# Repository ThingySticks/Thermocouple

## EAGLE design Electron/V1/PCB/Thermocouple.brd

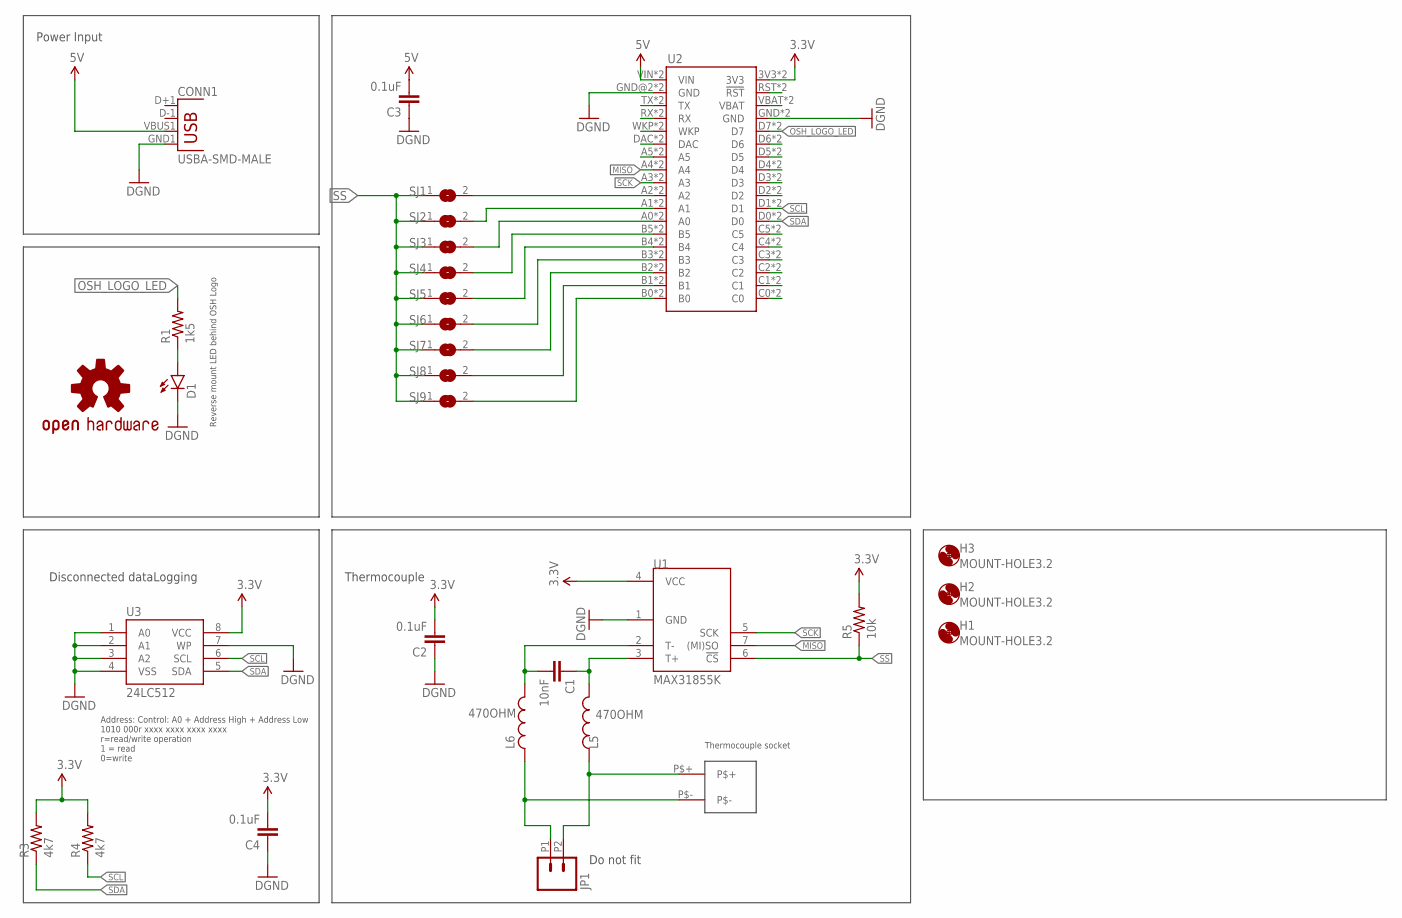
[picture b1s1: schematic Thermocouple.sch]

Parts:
C1: 10nF; 0805
C2, C3, C4: 0.1uF; 0805
CONN1: USBA-SMD-MALE; USB-A-SMT-MALE
D1: LED1206-BOTTOM; LED-1206-BOTTOM
H1, H2, H3: MOUNT-HOLE3.2; 3,2
JP1: M022.54MM_SCREWTERM; 1X02_2.54_SCREWTERM
JP2: THERMOCOUPLE_SOCKET_K-TYPE
L5, L6: 470OHM; 0805; FARNELL 1669726
LOGO1: OSHW-LOGOM; OSHW-LOGO-M
R1: 1k5; 1206
R3, R4: 4k7; 0805
R5: 10k; 0805
SJ1, SJ2, SJ3, SJ4, SJ5, SJ6, SJ7, SJ8, SJ9: SJ
U1: MAX31855K; SOIC8
U2: ELECTRONDUALNAMED; ELECTRON_SIMPLE_SILK_NAMES_DUAL
U3: 24LC512; SO08; FARNELL 1801220

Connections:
3.3V: C2.2, C4.2, R3.2, R4.2, R5.2, U1.4 (VCC), U2.3V3, U2.3V3_1 (3V3), U3.8 (VCC)
5V: C3.2, CONN1.VBUS1 (VBUS), U2.VIN, U2.VIN_1B (VIN)
DQ: SJ3.2, U2.A0, U2.A0_1 (A0)
GND: C2.1, C3.1, C4.1, CONN1.GND1 (GND), D1.C, U1.1 (GND), U2.GND, U2.GND@2 (GND), U2.GND_1 (GND), U2.GND_1B (GND), U3.1 (A0), U3.2 (A1), U3.3 (A2), U3.4 (VSS), U3.7 (WP)
MISO: U1.7 ((MI)SO), U2.A4, U2.A4_1 (A4)
MOSI: U2.A5, U2.A5_1 (A5)
unnamed: SJ2.2, U2.A1, U2.A1_1 (A1)
unnamed: U2.D2, U2.D2_1 (D2)
unnamed: U2.VBAT, U2.VBATT_1 (VBAT)
unnamed: U2.RST (!RST), U2.RST_1 (!RST)
unnamed: C1.2, L6.2, U1.2 (T-)
unnamed: U2.D3, U2.D3_1 (D3)
unnamed: C1.1, L5.2, U1.3 (T+)
unnamed: U2.D6, U2.D6_1 (D6)
unnamed: U2.D5, U2.D5_1 (D5)
unnamed: JP1.P1 (1), JP2.P$-, L6.1
unnamed: JP1.P2 (2), JP2.P$+, L5.1
unnamed: D1.A, R1.1
unnamed: U2.C1, U2.C1_1 (C1)
unnamed: U2.C5, U2.C5_1 (C5)
unnamed: U2.C4, U2.C4_1 (C4)
unnamed: U2.C3, U2.C3_1 (C3)
unnamed: U2.C2, U2.C2_1 (C2)
unnamed: U2.C0, U2.C0_1 (C0)
unnamed: U2.D4, U2.D4_1 (D4)
unnamed: U2.DAC, U2.DAC_1 (DAC)
unnamed: SJ1.2, U2.A2, U2.A2_1 (A2)
unnamed: SJ9.2, U2.B0, U2.B0_1 (B0)
unnamed: SJ8.2, U2.B1, U2.B1_1 (B1)
unnamed: SJ7.2, U2.B2, U2.B2_1 (B2)
unnamed: SJ6.2, U2.B3, U2.B3_1 (B3)
unnamed: SJ5.2, U2.B4, U2.B4_1 (B4)
unnamed: SJ4.2, U2.B5, U2.B5_1 (B5)
unnamed: U2.WKP, U2.WKP_1 (WKP)
unnamed: U2.RX, U2.RX_1 (RX)
unnamed: U2.TX, U2.TX_1 (TX)
OSH_LOGO_LED: R1.2, U2.D7, U2.D7_1 (D7)
SCK: U1.5 (SCK), U2.A3, U2.A3_1 (A3)
SCL: R4.1, U2.D1, U2.D1_1 (D1), U3.6 (SCL)
SDA: R3.1, U2.D0, U2.D0_1 (D0), U3.5 (SDA)
SS: R5.1, SJ1.1, SJ2.1, SJ3.1, SJ4.1, SJ5.1, SJ6.1, SJ7.1, SJ8.1, SJ9.1, U1.6 (!CS)

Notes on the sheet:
Disconnected dataLogging
Thermocouple
Power Input
Reverse mount LED behind OSH Logo
Address: Control: A0 + Address High + Address Low
Thermocouple socket
1010 000r xxxx xxxx xxxx xxxx r=read/write operation 1 = read 0=write
Do not fit

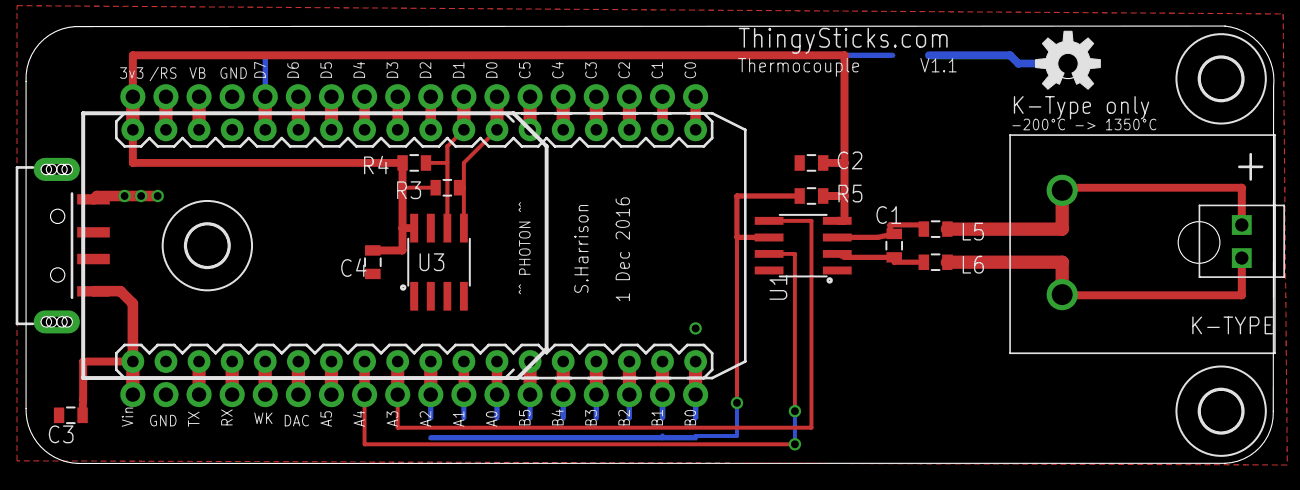
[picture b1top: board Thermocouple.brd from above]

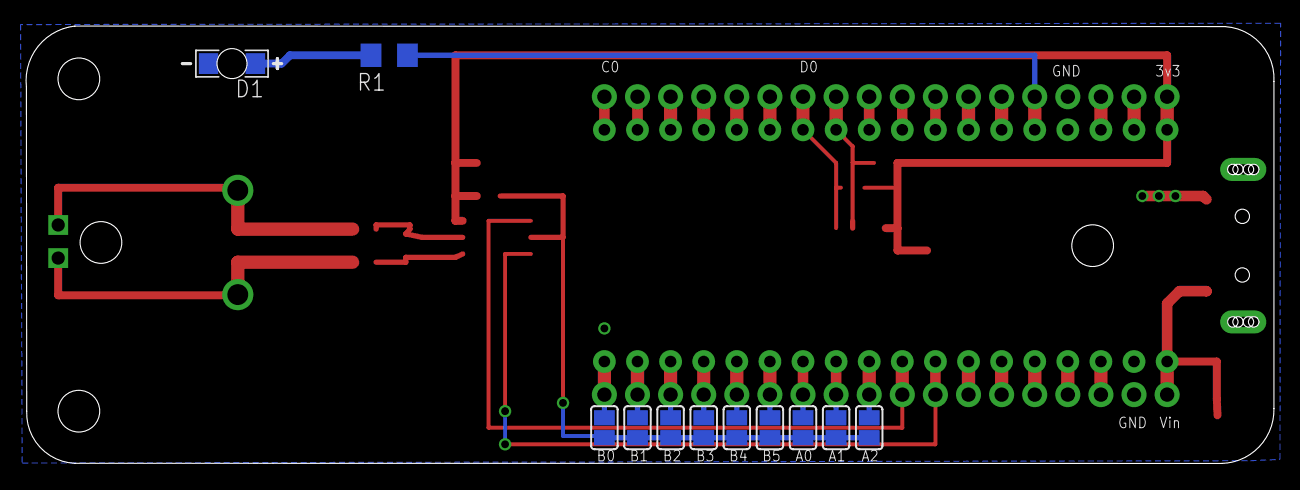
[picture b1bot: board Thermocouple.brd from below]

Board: 2 copper layers, 95.8 x 33.6 mm, 30 parts (11 on the bottom side), 41 nets.

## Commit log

2016-03-31 Iniital version as sent to DirtyPCBs.com
2016-11-20 Updated to V1.1 * Removed DS18B20 to focus on thermocouple only. * Added solder pads to allow select using A0/1/2 and B0-5 for stackable sensors with single photon/electron. * Removed battery connect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
2016-12-01 Improved sizes of silk screen labels.
    Added exports/pdfs and datasheet.
2016-12-22 Tidied up identifiers and added BOM
2017-01-04 Added sample code
2017-01-04 Fixed BOM json validation issues.
2017-01-04 Removed not implemented particle functions for now.
2017-01-04 Added schematic image.
2017-01-04 Fixed json validation issues for BOM.

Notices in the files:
parts and their libraries:
SparkFun-Connectors: Licensing: Creative Commons ShareAlike 4.0 International - https://creativecommons.org/licenses/by-sa/4.0
